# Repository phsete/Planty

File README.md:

# planty - a simple and compact moisture level sensor
This project is a simple and compact moisture level sensor based on an ESP32 C3 Module.

Check out the corresponding firmware at [https://github.com/phsete/planty-firmware](https://github.com/phsete/planty-firmware)!

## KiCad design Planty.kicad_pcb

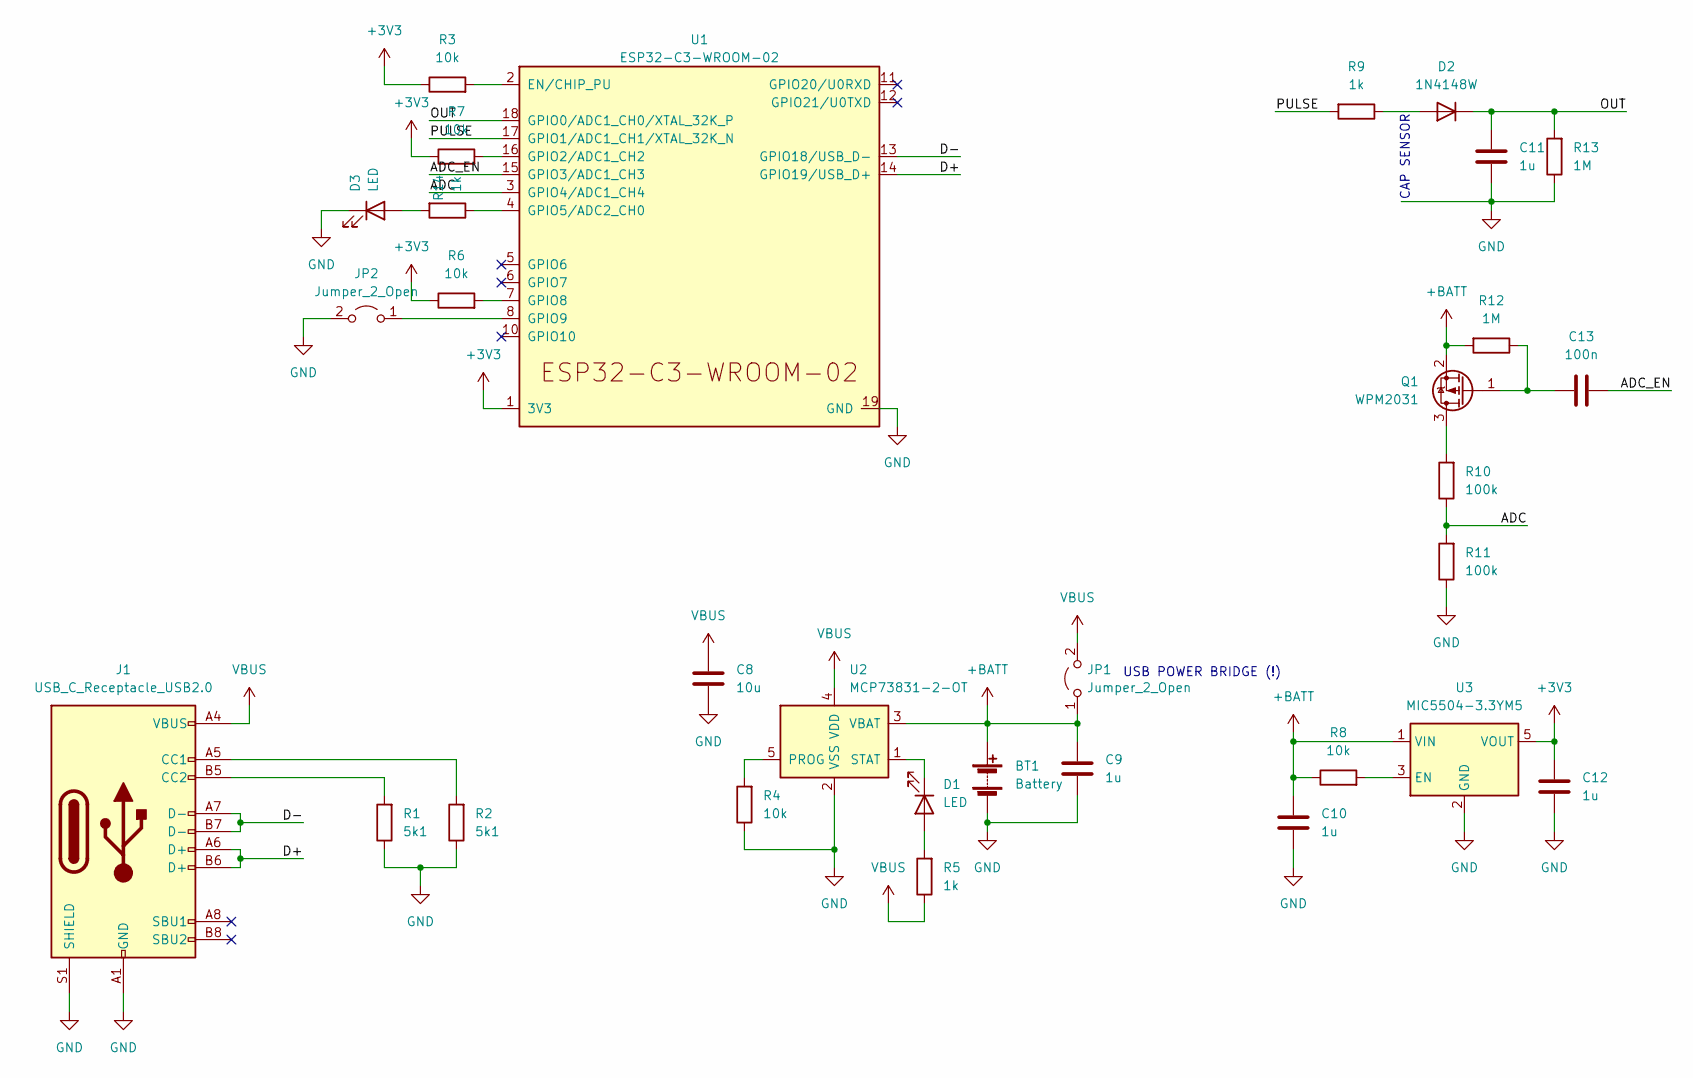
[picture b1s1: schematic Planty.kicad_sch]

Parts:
BT1: Battery; JST_PH_S2B-PH-SM4-TB_1x02-1MP_P2.00mm_Horizontal
C8: 10u; C_0805_2012Metric
C9, C10, C11, C12: 1u; C_0805_2012Metric
C13: 100n; C_0805_2012Metric
D1, D3: LED; LED_0805_2012Metric
D2: 1N4148W; D_SOD-123
J1: USB_C_Receptacle_USB2.0; USB_C_Receptacle_GCT_USB4105-xx-A_16P_TopMnt_Horizontal
JP1, JP2: Jumper_2_Open; SolderJumper-2_P1.3mm_Open_RoundedPad1.0x1.5mm
Q1: WPM2031; SOT-723
R1, R2: 5k1; R_0805_2012Metric
R3, R4, R6, R7, R8: 10k; R_0805_2012Metric
R5, R9, R14: 1k; R_0805_2012Metric
R10, R11: 100k; R_0805_2012Metric
R12, R13: 1M; R_0805_2012Metric
U1: ESP32-C3-WROOM-02
U2: MCP73831-2-OT; SOT-23-5
U3: MIC5504-3.3YM5; SOT-23-5

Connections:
+3V3: C12.2, R3.1, R6.1, R7.1, U1.1 (3V3), U3.5 (VOUT)
+BATT: BT1.1 (+), C9.2, C10.2, JP1.1 (A), Q1.2 (S), R8.1, R12.2, U2.3 (VBAT), U3.1 (VIN)
/ADC: R10.1, R11.2, U1.3 (GPIO4/ADC1_CH4)
/ADC_EN: C13.1, U1.15 (GPIO3/ADC1_CH3)
/D+: J1.A6 (D+), J1.B6 (D+), U1.14 (GPIO19/USB_D+)
/D-: J1.A7 (D-), J1.B7 (D-), U1.13 (GPIO18/USB_D-)
/OUT: C11.2, D2.1 (K), R13.2, U1.18 (GPIO0/ADC1_CH0/XTAL_32K_P)
/PULSE: R9.2, U1.17 (GPIO1/ADC1_CH1/XTAL_32K_N)
GND: BT1.2 (-), C8.1, C9.1, C10.1, C11.1, C12.1, D3.1 (K), J1.A1 (GND), J1.A12 (GND), J1.B1 (GND), J1.B12 (GND), J1.S1 (SHIELD), JP2.2 (B), R1.1, R2.1, R4.1, R11.1, R13.1, U1.9 (GND), U1.19 (GND), U2.2 (VSS), U3.2 (GND)
unnamed: C13.2, Q1.1 (G), R12.1
unnamed: D1.1 (K), U2.1 (STAT)
unnamed: D1.2 (A), R5.2
unnamed: D2.2 (A), R9.1
unnamed: D3.2 (A), R14.2
unnamed: J1.A5 (CC1), R2.2
unnamed: J1.B5 (CC2), R1.2
unnamed: JP2.1 (A), U1.8 (GPIO9)
unnamed: Q1.3 (D), R10.2
unnamed: R3.2, U1.2 (EN/CHIP_PU)
unnamed: R4.2, U2.5 (PROG)
unnamed: R6.2, U1.7 (GPIO8)
unnamed: R7.2, U1.16 (GPIO2/ADC1_CH2)
unnamed: R8.2, U3.3 (EN)
unnamed: R14.1, U1.4 (GPIO5/ADC2_CH0)
VBUS: C8.2, J1.A4 (VBUS), J1.A9 (VBUS), J1.B4 (VBUS), J1.B9 (VBUS), JP1.2 (B), R5.1, U2.4 (VDD)

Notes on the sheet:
CAP SENSOR
USB POWER BRIDGE (!)

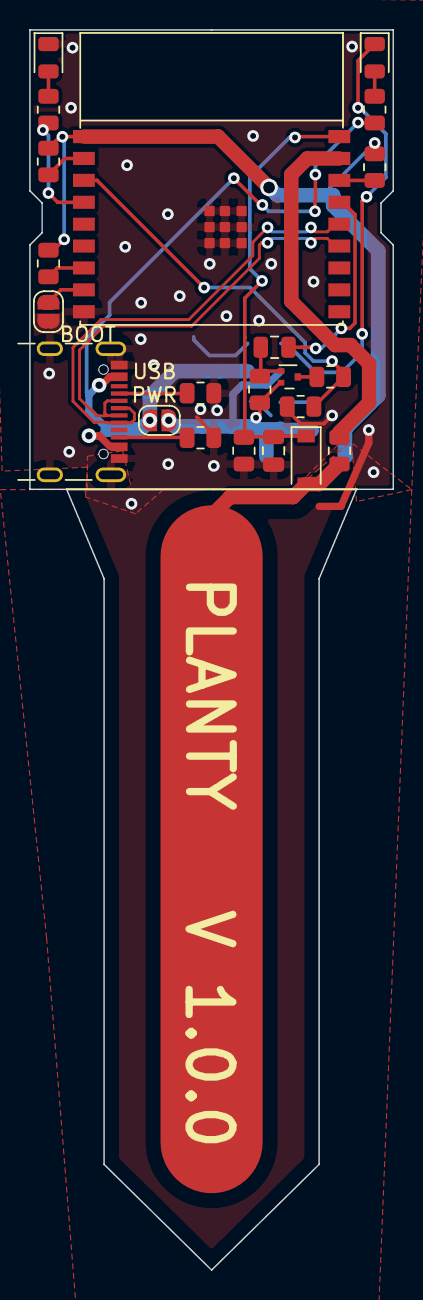
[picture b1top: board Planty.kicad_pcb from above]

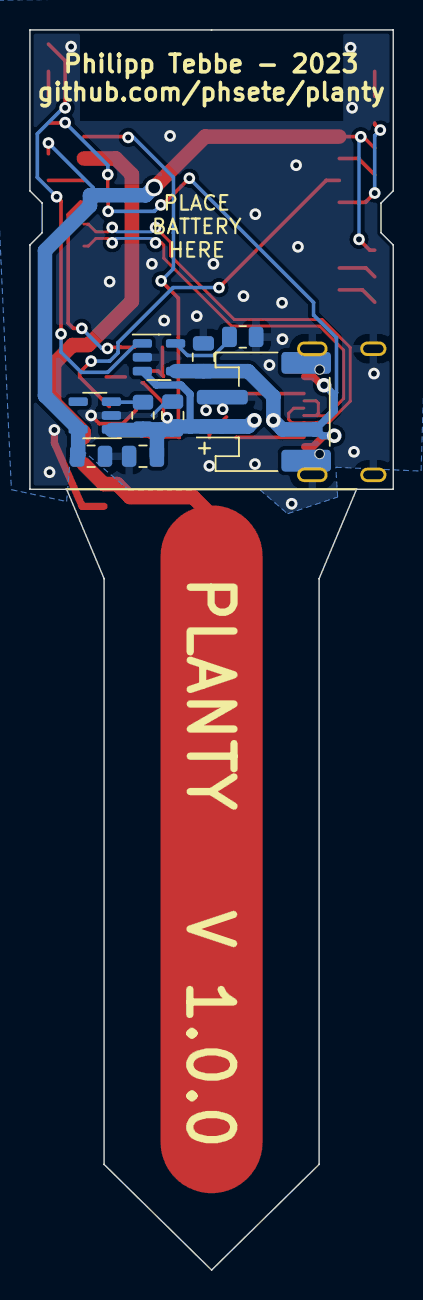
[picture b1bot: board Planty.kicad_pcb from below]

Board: 2 copper layers, 24.9 x 85.0 mm, 31 parts (9 on the bottom side), 25 nets.

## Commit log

2023-01-09 first draft
2023-01-10 finished v1.0.0
2023-01-10 add image
